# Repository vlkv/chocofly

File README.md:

# The Chocofly keyboard

The Chocofly is an ergonomic monosplit keyboard with 4x6 column staggered keys,
4 thumb keys and 2 additional inner keys for the index finger (60 keys total) plus one rotary encoder.

The main idea of the Chocofly is to be [thin](https://imgur.com/a/kJ5HPdX) and suitable for "sonshi"-style usage (putting it [ontop the laptop keyboard](https://imgur.com/gallery/Bps65YA)). It is also pretty minimalistic - no LEDs/OLEDs/labels on keycaps/wires... and in my build it even has no case. It's just a pcb with switches on top of it and small silicone legs on the bottom. And this setup works pefectly! Well, for me at least.

Notable features:
- Kailh Choc V1 switches support (both hotswap and non-hotswap - in one PCB).
- Non-agressive column stagger with just a little bit fan-angled 5th and 6th columns.
- Fancy-shmancy "flying" design.

Chocofly v3 PCB.

Chocofly v2 PCB.

Chocofly v1 PCB.

Chocofly v1.

## Layout tester

TODO.

## Gerber files
* [Version 3.0](https://github.com/vlkv/chocofly/tree/v3.0).
  * [PCB](https://github.com/vlkv/chocofly/blob/v3.0/pcb/chocofly_v3_0_pcb.zip) Status: tested, OK.
  * Dimensions 304x133.5mm (or 304x116.2mm without number row)
  * 17.5x17.5mm switch spacing (for Chosfox keycaps).
* [Version 2.0](https://github.com/vlkv/chocofly/tree/v2.0).
  * [PCB](https://github.com/vlkv/chocofly/blob/v2.0/pcb/chocofly_v2_0_pcb.zip) Status: tested, OK.
  * Dimensions: 317x133.4mm (or 317x116.7mm without number row)
  * 19x18mm switch spacing (for MKUltra keycaps, Chosfox will fit too).
* [Version 1.1](https://github.com/vlkv/chocofly/tree/v1.1).
  * [PCB](https://github.com/vlkv/chocofly/blob/v1.1/pcb/chocofly_v1_1_pcb.zip).
  * [top cover](https://github.com/vlkv/chocofly/blob/v1.0/top_cover/chocofly_v1_0_top_cover.zip) (Same as v1.0).
  * [bottom plate](https://github.com/vlkv/chocofly/blob/master/bottom_plate/chocofly_v1_0_bottom_plate.zip) (Same as v1.0).
* [Version 1.0](https://github.com/vlkv/chocofly/tree/v1.0).
  * Known issues:
    * https://github.com/vlkv/chocofly/issues/2
  * [PCB](https://github.com/vlkv/chocofly/blob/v1.0/pcb/chocofly_v1_0_pcb.zip).
  * [top cover](https://github.com/vlkv/chocofly/blob/v1.0/top_cover/chocofly_v1_0_top_cover.zip).
  * [bottom plate](https://github.com/vlkv/chocofly/blob/master/bottom_plate/chocofly_v1_0_bottom_plate.zip).

## Parts list

Is [here](parts_list.md).

## Build instructions

See similar https://github.com/vlkv/avalanche#build-instructions

A few tips specific to the Chocofly:
- You have to make the bottom of the keyboad as flat as possible. Because you will need to glue rubber sheet on it. That is why you better
  * cut the switches' legs before soldering. Insert the switch into its place, cut the legs to the optimal length, then solder them.
  * do not cut the central plastic shafts of the switches!
  * use SMD diodes instead of throgh-hole ones.
- Using 2mm think PCB should be a better option than 1.6mm, because it will hide the switches' shafts too.

## Firmware
* Notes about the [default keyboard layout](https://github.com/vlkv/chocofly/blob/master/docs/layout.md).
* [ZMK](https://github.com/vlkv/chocofly-zmk-config) for wireless builds.
* [QMK](https://github.com/vlkv/qmk_firmware/tree/master/keyboards/chocofly) for wired builds.

## Chat group

There is a [chat group in Telegram](https://t.me/avalanche_kb), where you may chat about the project or ask some questions/help.

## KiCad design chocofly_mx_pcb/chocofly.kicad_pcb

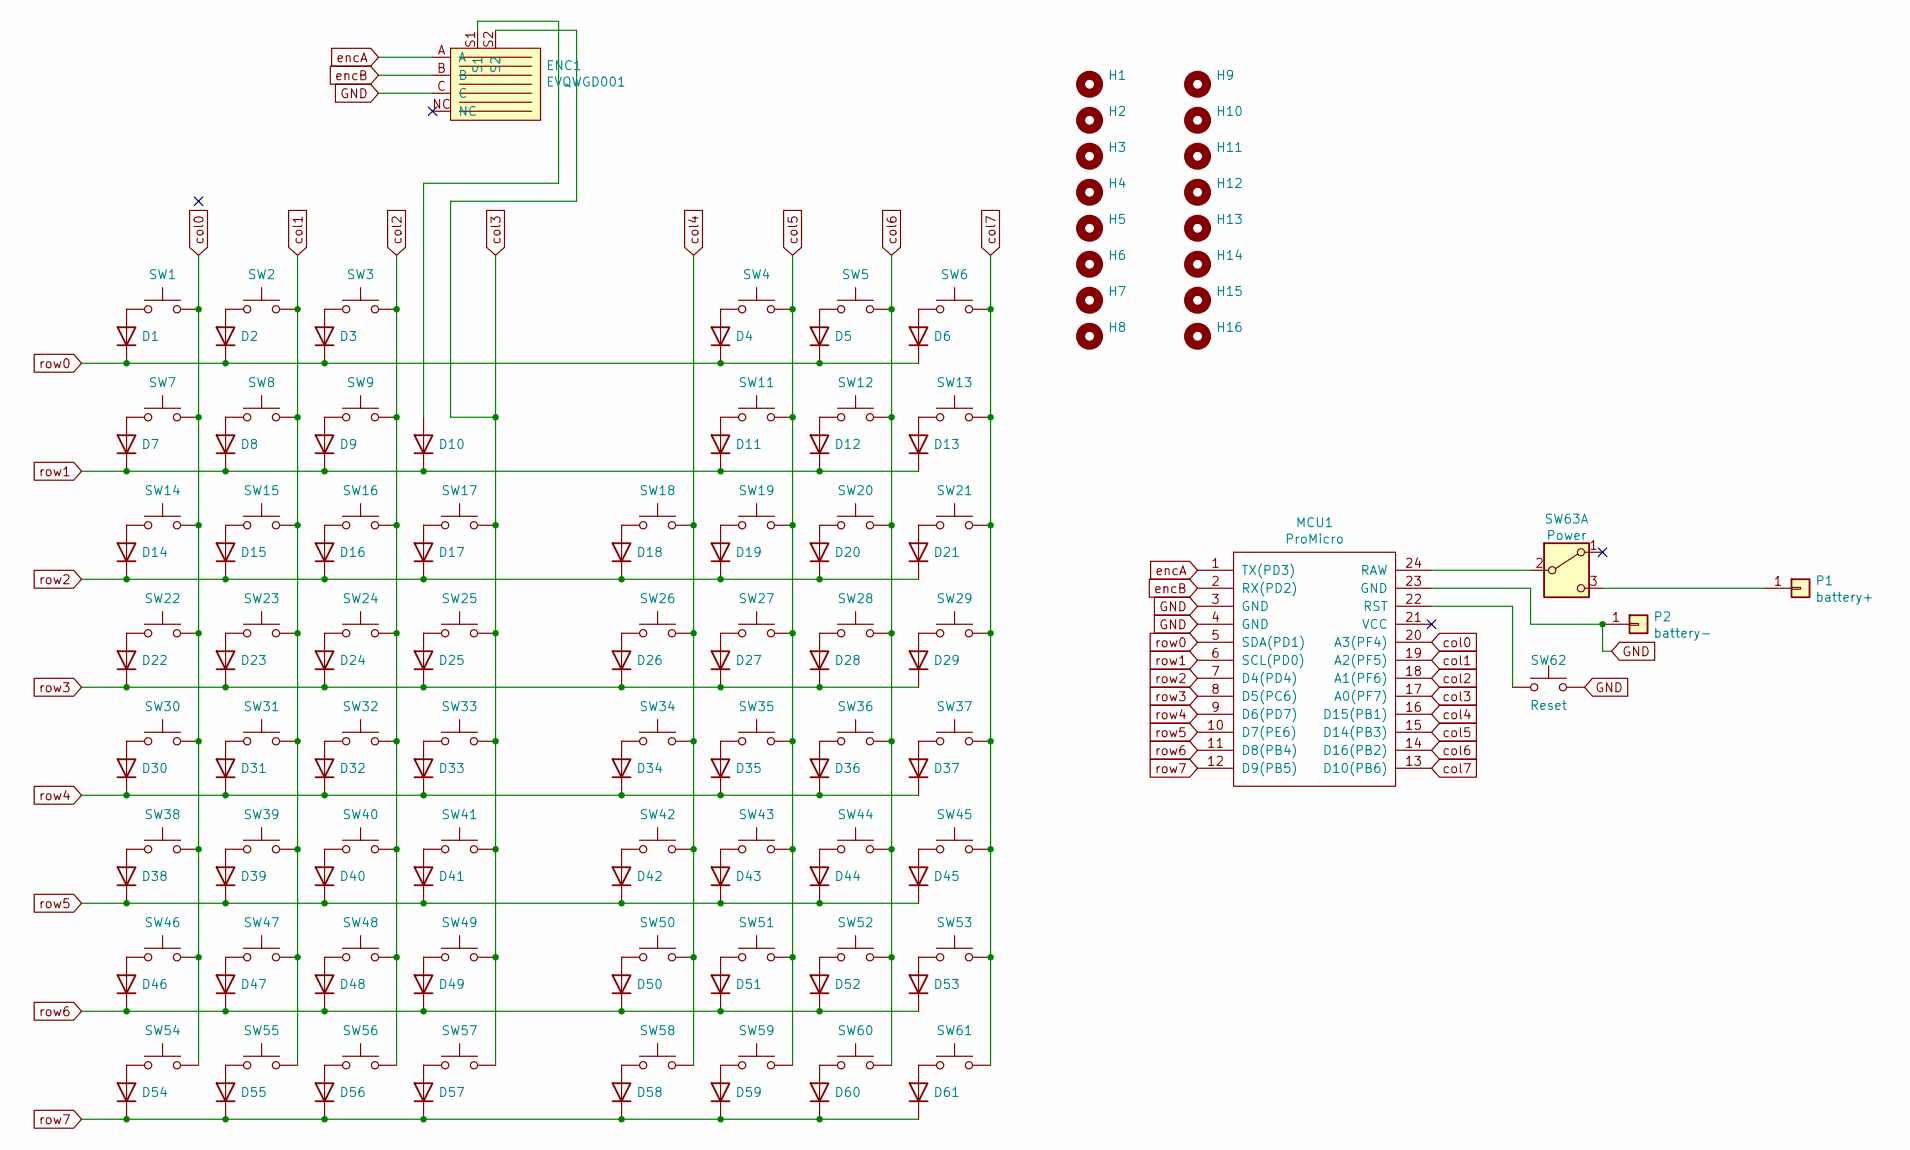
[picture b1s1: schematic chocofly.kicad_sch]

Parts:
D1, D2, D3, D4, D5, D6, D7, D8, D9, D10, D11, D12, D13, D14, D15, D16, D17, D18, D19, D20, D21, D22, D23, D24, D25, D26, D27, D28, D29, D30, D31, D32, D33, D34, D35, D36, D37, D38, D39, D40, D41, D42, D43, D44, D45, D46, D47, D48, D49, D50, D51, D52, D53, D54, D55, D56, D57, D58, D59, D60, D61: 1N4148; diode_TH_SMD
ENC1: EVQWGD001
H1, H2, H3, H4, H5, H6, H7, H8, H9, H10, H11, H12, H13, H14, H15, H16: MountingHole; MountingHole_2.2mm_M2
MCU1: ProMicro
P1: battery+; 1pin_conn
P2: battery-; 1pin_conn
SW1, SW2, SW3, SW4, SW5, SW6, SW7, SW8, SW9, SW11, SW12, SW13, SW14, SW15, SW16, SW17, SW18, SW19, SW20, SW21, SW22, SW23, SW24, SW25, SW26, SW27, SW28, SW29, SW30, SW31, SW32, SW33, SW34, SW35, SW36, SW37, SW38, SW39, SW40, SW41, SW42, SW43, SW44, SW45, SW46, SW47, SW48, SW49, SW50, SW51, SW52, SW53, SW54, SW55, SW56, SW57, SW58, SW59, SW60, SW61: SW_Push; CherryMX_MidHeight_Hotswap_1u
SW62: Reset; Switch_Reset_THT
SW63: Power; Switch_MSK-12C01-07

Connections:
GND: ENC1.C, MCU1.3 (GND), MCU1.4 (GND), MCU1.23 (GND), P2.1, SW62.2
unnamed: D1.2 (A), SW1.1
unnamed: D2.2 (A), SW2.1
unnamed: D3.2 (A), SW3.1
unnamed: D4.2 (A), SW4.1
unnamed: D5.2 (A), SW5.1
unnamed: D6.2 (A), SW6.1
unnamed: D7.2 (A), SW7.1
unnamed: D8.2 (A), SW8.1
unnamed: D9.2 (A), SW9.1
unnamed: D10.2 (A), ENC1.S1
unnamed: D11.2 (A), SW11.1
unnamed: D12.2 (A), SW12.1
unnamed: D13.2 (A), SW13.1
unnamed: D14.2 (A), SW14.1
unnamed: D15.2 (A), SW15.1
unnamed: D16.2 (A), SW16.1
unnamed: D17.2 (A), SW17.1
unnamed: D18.2 (A), SW18.1
unnamed: D19.2 (A), SW19.1
unnamed: D20.2 (A), SW20.1
unnamed: D21.2 (A), SW21.1
unnamed: D22.2 (A), SW22.1
unnamed: D23.2 (A), SW23.1
unnamed: D24.2 (A), SW24.1
unnamed: D25.2 (A), SW25.1
unnamed: D26.2 (A), SW26.1
unnamed: D27.2 (A), SW27.1
unnamed: D28.2 (A), SW28.1
unnamed: D29.2 (A), SW29.1
unnamed: D30.2 (A), SW30.1
unnamed: D31.2 (A), SW31.1
unnamed: D32.2 (A), SW32.1
unnamed: D33.2 (A), SW33.1
unnamed: D34.2 (A), SW34.1
unnamed: D35.2 (A), SW35.1
unnamed: D36.2 (A), SW36.1
unnamed: D37.2 (A), SW37.1
unnamed: D38.2 (A), SW38.1
unnamed: D39.2 (A), SW39.1
unnamed: D40.2 (A), SW40.1
unnamed: D41.2 (A), SW41.1
unnamed: D42.2 (A), SW42.1
unnamed: D43.2 (A), SW43.1
unnamed: D44.2 (A), SW44.1
unnamed: D45.2 (A), SW45.1
unnamed: D46.2 (A), SW46.1
unnamed: D47.2 (A), SW47.1
unnamed: D48.2 (A), SW48.1
unnamed: D49.2 (A), SW49.1
unnamed: D50.2 (A), SW50.1
unnamed: D51.2 (A), SW51.1
unnamed: D52.2 (A), SW52.1
unnamed: D53.2 (A), SW53.1
unnamed: D54.2 (A), SW54.1
unnamed: D55.2 (A), SW55.1
unnamed: D56.2 (A), SW56.1
unnamed: D57.2 (A), SW57.1
unnamed: D58.2 (A), SW58.1
unnamed: D59.2 (A), SW59.1
unnamed: D60.2 (A), SW60.1
unnamed: D61.2 (A), SW61.1
unnamed: MCU1.24 (RAW), SW63.2 (B)
unnamed: MCU1.22 (RST), SW62.1
unnamed: P1.1, SW63.3 (C)
col0: MCU1.20 (A3(PF4)), SW1.2, SW7.2, SW14.2, SW22.2, SW30.2, SW38.2, SW46.2, SW54.2
col1: MCU1.19 (A2(PF5)), SW2.2, SW8.2, SW15.2, SW23.2, SW31.2, SW39.2, SW47.2, SW55.2
col2: MCU1.18 (A1(PF6)), SW3.2, SW9.2, SW16.2, SW24.2, SW32.2, SW40.2, SW48.2, SW56.2
col3: ENC1.S2, MCU1.17 (A0(PF7)), SW17.2, SW25.2, SW33.2, SW41.2, SW49.2, SW57.2
col4: MCU1.16 (D15(PB1)), SW18.2, SW26.2, SW34.2, SW42.2, SW50.2, SW58.2
col5: MCU1.15 (D14(PB3)), SW4.2, SW11.2, SW19.2, SW27.2, SW35.2, SW43.2, SW51.2, SW59.2
col6: MCU1.14 (D16(PB2)), SW5.2, SW12.2, SW20.2, SW28.2, SW36.2, SW44.2, SW52.2, SW60.2
col7: MCU1.13 (D10(PB6)), SW6.2, SW13.2, SW21.2, SW29.2, SW37.2, SW45.2, SW53.2, SW61.2
encA: ENC1.A, MCU1.1 (TX(PD3))
encB: ENC1.B, MCU1.2 (RX(PD2))
row0: D1.1 (K), D2.1 (K), D3.1 (K), D4.1 (K), D5.1 (K), D6.1 (K), MCU1.5 (SDA(PD1))
row1: D7.1 (K), D8.1 (K), D9.1 (K), D10.1 (K), D11.1 (K), D12.1 (K), D13.1 (K), MCU1.6 (SCL(PD0))
row2: D14.1 (K), D15.1 (K), D16.1 (K), D17.1 (K), D18.1 (K), D19.1 (K), D20.1 (K), D21.1 (K), MCU1.7 (D4(PD4))
row3: D22.1 (K), D23.1 (K), D24.1 (K), D25.1 (K), D26.1 (K), D27.1 (K), D28.1 (K), D29.1 (K), MCU1.8 (D5(PC6))
row4: D30.1 (K), D31.1 (K), D32.1 (K), D33.1 (K), D34.1 (K), D35.1 (K), D36.1 (K), D37.1 (K), MCU1.9 (D6(PD7))
row5: D38.1 (K), D39.1 (K), D40.1 (K), D41.1 (K), D42.1 (K), D43.1 (K), D44.1 (K), D45.1 (K), MCU1.10 (D7(PE6))
row6: D46.1 (K), D47.1 (K), D48.1 (K), D49.1 (K), D50.1 (K), D51.1 (K), D52.1 (K), D53.1 (K), MCU1.11 (D8(PB4))
row7: D54.1 (K), D55.1 (K), D56.1 (K), D57.1 (K), D58.1 (K), D59.1 (K), D60.1 (K), D61.1 (K), MCU1.12 (D9(PB5))

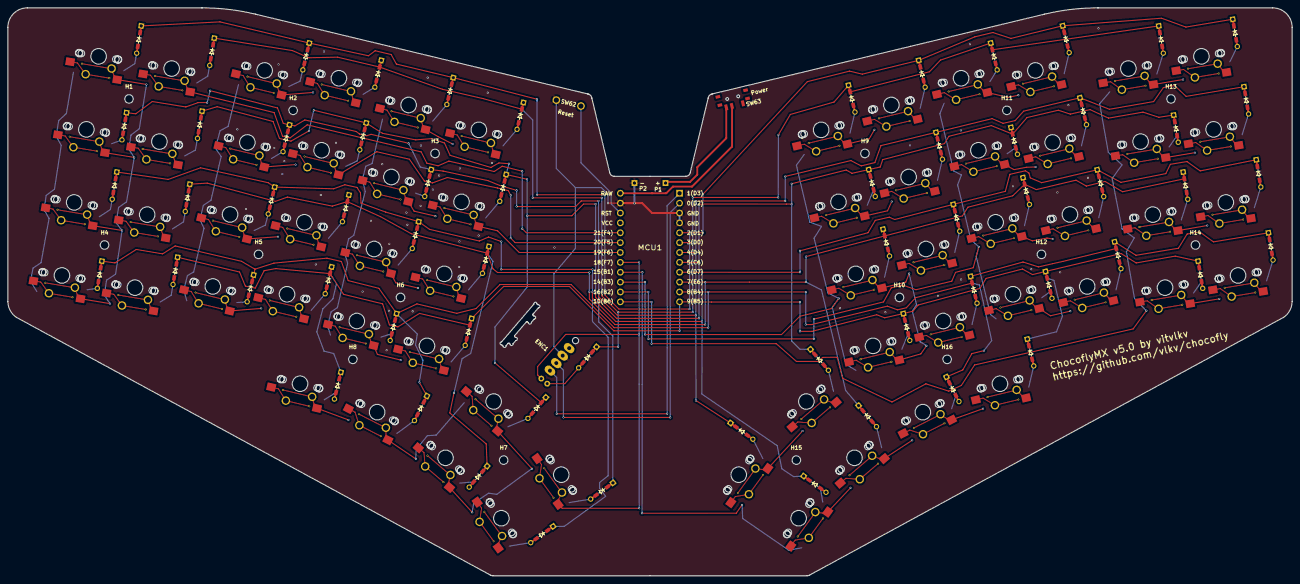
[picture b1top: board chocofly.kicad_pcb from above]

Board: 2 copper layers, 330.4 x 146.1 mm, 143 parts (0 on the bottom side), 83 nets.

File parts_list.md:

## Parts list

| #  | Name                                       | Quantity | Example URL                                           |
|----|--------------------------------------------|----------|-------------------------------------------------------|
| 1  | The Chocofly PCB                           | 1        | https://github.com/vlkv/chocofly/tree/master/pcb      |
| 2  | ProMicro (ATmega32U4 5V/16MHz)             | 1        | https://aliexpress.ru/item/2010847161.html            |
| 3  | Sockets for ProMicro 3.5mm                 | 2        | https://aliexpress.ru/item/32360715483.html           |
| 4  | Diode 1N4148 (SMD or through hole)         | 61       | https://aliexpress.ru/item/32881432301.html           |
| 5  | Reset button (DIP switch)                  | 1        | https://aliexpress.ru/item/4000209910403.html (or maybe https://aliexpress.ru/item/32923215854.html)         |
| 6  | Rotary encoder EVQWGD001 (optional)        | 1        | https://aliexpress.ru/item/4001293888953.html         |
| 7  | Keyboard switch (Kailh Choc V1)            | 60       | https://aliexpress.ru/item/32838369089.html           |
| 8  | Kailh Choc hotswap sockets (optional)      | 60       | https://aliexpress.ru/item/33023283633.html           |
| 9  | Keycaps set (Kailh Choc V1 compatible)     | 1        | https://mkultra.click/mbk-choc-keycaps (recommended) or cheaper https://aliexpress.ru/item/32979973961.html (take white or black, but not transparent)                |
| 10 | Bumpons for bottom plate (set)             | 1        | https://aliexpress.ru/item/32680543746.html           |


If you want wireless build, then instead of ProMicro you need nice!nano or
nRFMicro or some other compartible wireless ProMicro drop-in replacement. And also a micro switch to cut off the power:

| #  | Name                                       | Quantity | Example URL                                           |
|----|--------------------------------------------|----------|-------------------------------------------------------|
| 11 | nice!nano controller                       | 1        | https://nicekeyboards.com/nice-nano                   |
| 12 | nRFMicro                                   | 1        | https://github.com/joric/nrfmicro                     |
| 13 | Power micro switch MSK-12C01-07            | 1        | https://aliexpress.ru/item/32963237441.html           |
| 14 | Li-Po Rechargeable Battery                 | 1        | https://aliexpress.ru/item/32831998939.html           | 


If you want sandwich "case", then you will need some of:

| #  | Name                                       | Quantity | Example URL                                               |
|----|--------------------------------------------|----------|-----------------------------------------------------------|
| 15 | Top cover                                  | 1        | https://github.com/vlkv/chocofly/tree/master/top_cover    |
| 16 | Bottom plate                               | 1        | https://github.com/vlkv/chocofly/tree/master/bottom_plate |
| 17 | M2 screws 3mm                              | 15       | https://aliexpress.ru/item/32976056190.html               |
| 18 | M2 standoffs ?mm                           | 15       | https://aliexpress.ru/item/32597776358.html               |

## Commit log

2021-09-26 Added first files
2021-09-26 Working on the PCB
2021-09-26 Aligned all the switches
2021-09-26 Aligned diodes
2021-09-26 Ready to shape the thumb cluster
2021-09-26 WIP on thumb cluster
2021-09-26 Shaped the vertical stagger
2021-09-26 Shaped the keyboard in general
2021-09-26 Fine-aligned upper thumb buttons
2021-09-26 Added rotary encoder
2021-09-26 Added promicro
2021-09-26 Trying to implement more sophisticated row/col scheme
2021-09-26 ProMicro extended with 2 more pins
2021-09-26 WIP on keyboard matrix
2021-09-26 Added more symbols to the schema
2021-09-26 Made footprints one-sided
2021-09-26 Renumbered switches on the pcb
2021-09-26 Working
2021-09-26 Changed angle between halves
2021-09-27 Better edge cuts for 'sonshi' style
2021-09-27 Changed switch footprint
2021-09-27 Reversible footprint for diode
2021-09-27 Repositioned all diodes
2021-09-27 Routing tracks
2021-09-27 Routing...
2021-09-28 Right half is generally routed
2021-09-28 Routing
2021-09-28 Minor changes
2021-09-28 Corrected tracks by perimeter
2021-09-28 New edge cuts
2021-09-28 Mounting holes
2021-10-03 Working on mounting holes
2021-10-03 Edges
2021-10-03 Removed redundant comments lines
2021-10-03 Added pimoroni sketch footprint
2021-10-03 Added horizontal encoder footprint
2021-10-03 Added horizontal encoder to the schema
2021-10-04 Horizontal encoder
2021-10-05 Minor rotes fix
2021-10-06 Outer edges
2021-10-06 Changed the edges
2021-10-06 Shortened the overal length
2021-10-06 Bottom plate draft
2021-10-06 Top Cover
2021-10-06 Plates and covers
2021-10-09 Beautified some tracks
2021-10-09 Moving mounting holes
2021-10-10 Mountin holes
2021-10-10 Removed extra holes
2021-10-10 Done with mounting holes, I guess.
2021-10-13 Making the hole for the encoder optional
2021-10-13 Introduced another switch spacing 19x18mm
2021-10-13 New layout
2021-10-14 Routing the tracks...
2021-10-14 Routing the tracks
2021-10-15 Routed the columns
2021-10-15 Looks like all tracks routed
2021-10-15 Polishing
2021-10-15 Removed unused footprints
2021-10-15 Made the board a bit wider
2021-10-15 Working on top cover
2021-10-15 Top plate is done
2021-10-15 Found a good name at last
2021-10-16 Renamed everything to chocofly
2021-10-16 Generated gerbers for v1.0
2021-11-15 Create LICENSE
2021-11-15 Added readme and an image
2021-11-15 Changed the image
2021-11-15 Readme update
2021-11-15 readme
2021-11-15 Fixed url
2021-11-15 one more image
2021-11-27 Updated the main photo
2021-11-30 Created parts list
2021-11-30 Parts list update
2021-11-30 fixed table
2021-11-30 fix of table
2021-12-01 Reverting promicro in progress
2021-12-05 Reverting promicro in progress...
2021-12-05 Reverse the ProMicro #2 IS DONE
2021-12-05 Minor improvements
2021-12-05 Gerbers v1.1
2021-12-05 Updated image (now with encoder)
2021-12-05 Docs update
2021-12-05 Gerbers for bottom plate
2021-12-05 Updated docs
2022-12-04 Footprint for chocfox keycaps
2022-12-04 v2 wip
2022-12-04 General layout is ready
2022-12-13 Added first notes about my layout
2022-12-17 Added some images
2022-12-17 Image
2022-12-17 Images
2022-12-17 Renamed a file
2023-01-07 Added comment about angles
2023-01-07 Added footprint for mkultra keycap spacing
2023-01-13 General design is done
2023-01-13 Edge cuts are so cool.
2023-01-13 Added one more encoder
2023-01-13 Ready to wire
2023-01-13 Wiring...
2023-01-14 Routing the right half
2023-01-14 All connected
2023-01-14 All cleaned up
2023-01-15 New break-off way
2023-01-15 New egde cuts
2023-01-15 Minor edge cut improves
2023-01-15 V2 is done
2023-01-15 Generated gerbers
2023-01-15 Lots of minor changes
2023-01-15 Updated gerbers
2023-01-15 Fixed pcb v2 after incorrect conflicts resolve
2024-08-24 started work on v3 (for chosfox keycaps and Mac Air 13'')
2024-08-27 Rearranged the new layout with square footprint of 17.5 mm for chosfox keycap
2024-08-27 deleted old elements from pcb
2024-08-27 updated diode footprint
2024-08-27 edge cuts are consistent
2024-08-27 added secondary power switch
2024-08-28 deleted pcb2 dir
2024-08-28 additional pads for diodes
2024-08-28 wiring in progress
2024-08-29 routing wip
2024-08-29 checks ok
2024-08-30 cleaned up tracks and vias
2024-08-31 added seaguls
2024-08-31 I guess v3 is generally done
2024-08-31 Plot the gerbers
2024-09-02 filledzones&rondtracks
2025-01-07 Copied pcb to pcb_mx dir
2025-01-07 WIP on mx version of chocofly
2025-01-07 labels
2025-03-27 wip on chocomx
2025-04-06 added encoder back
2025-04-06 mounting holes added
2025-04-06 pcb is generally done
2025-04-06 renamed a lot
2025-04-06 top_plate
2025-04-06 bottom_plate
2025-04-16 using non-hotswap footprint
2026-05-10 done
